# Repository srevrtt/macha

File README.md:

# Macha

Macha is currently a Work-In-Progress (WIP). I have not completely written this README
yet because this project is nowhere close to being finished and therefore I don't know
what features the eventual release will/will not have.

But basically, Macha will be a hypersonic, secure, and easy-to-use database/spreadhseet
application for my own personal and business use. The goal for now is not to make this
perfect for everyone; just trying to make it perfect for me first. :)

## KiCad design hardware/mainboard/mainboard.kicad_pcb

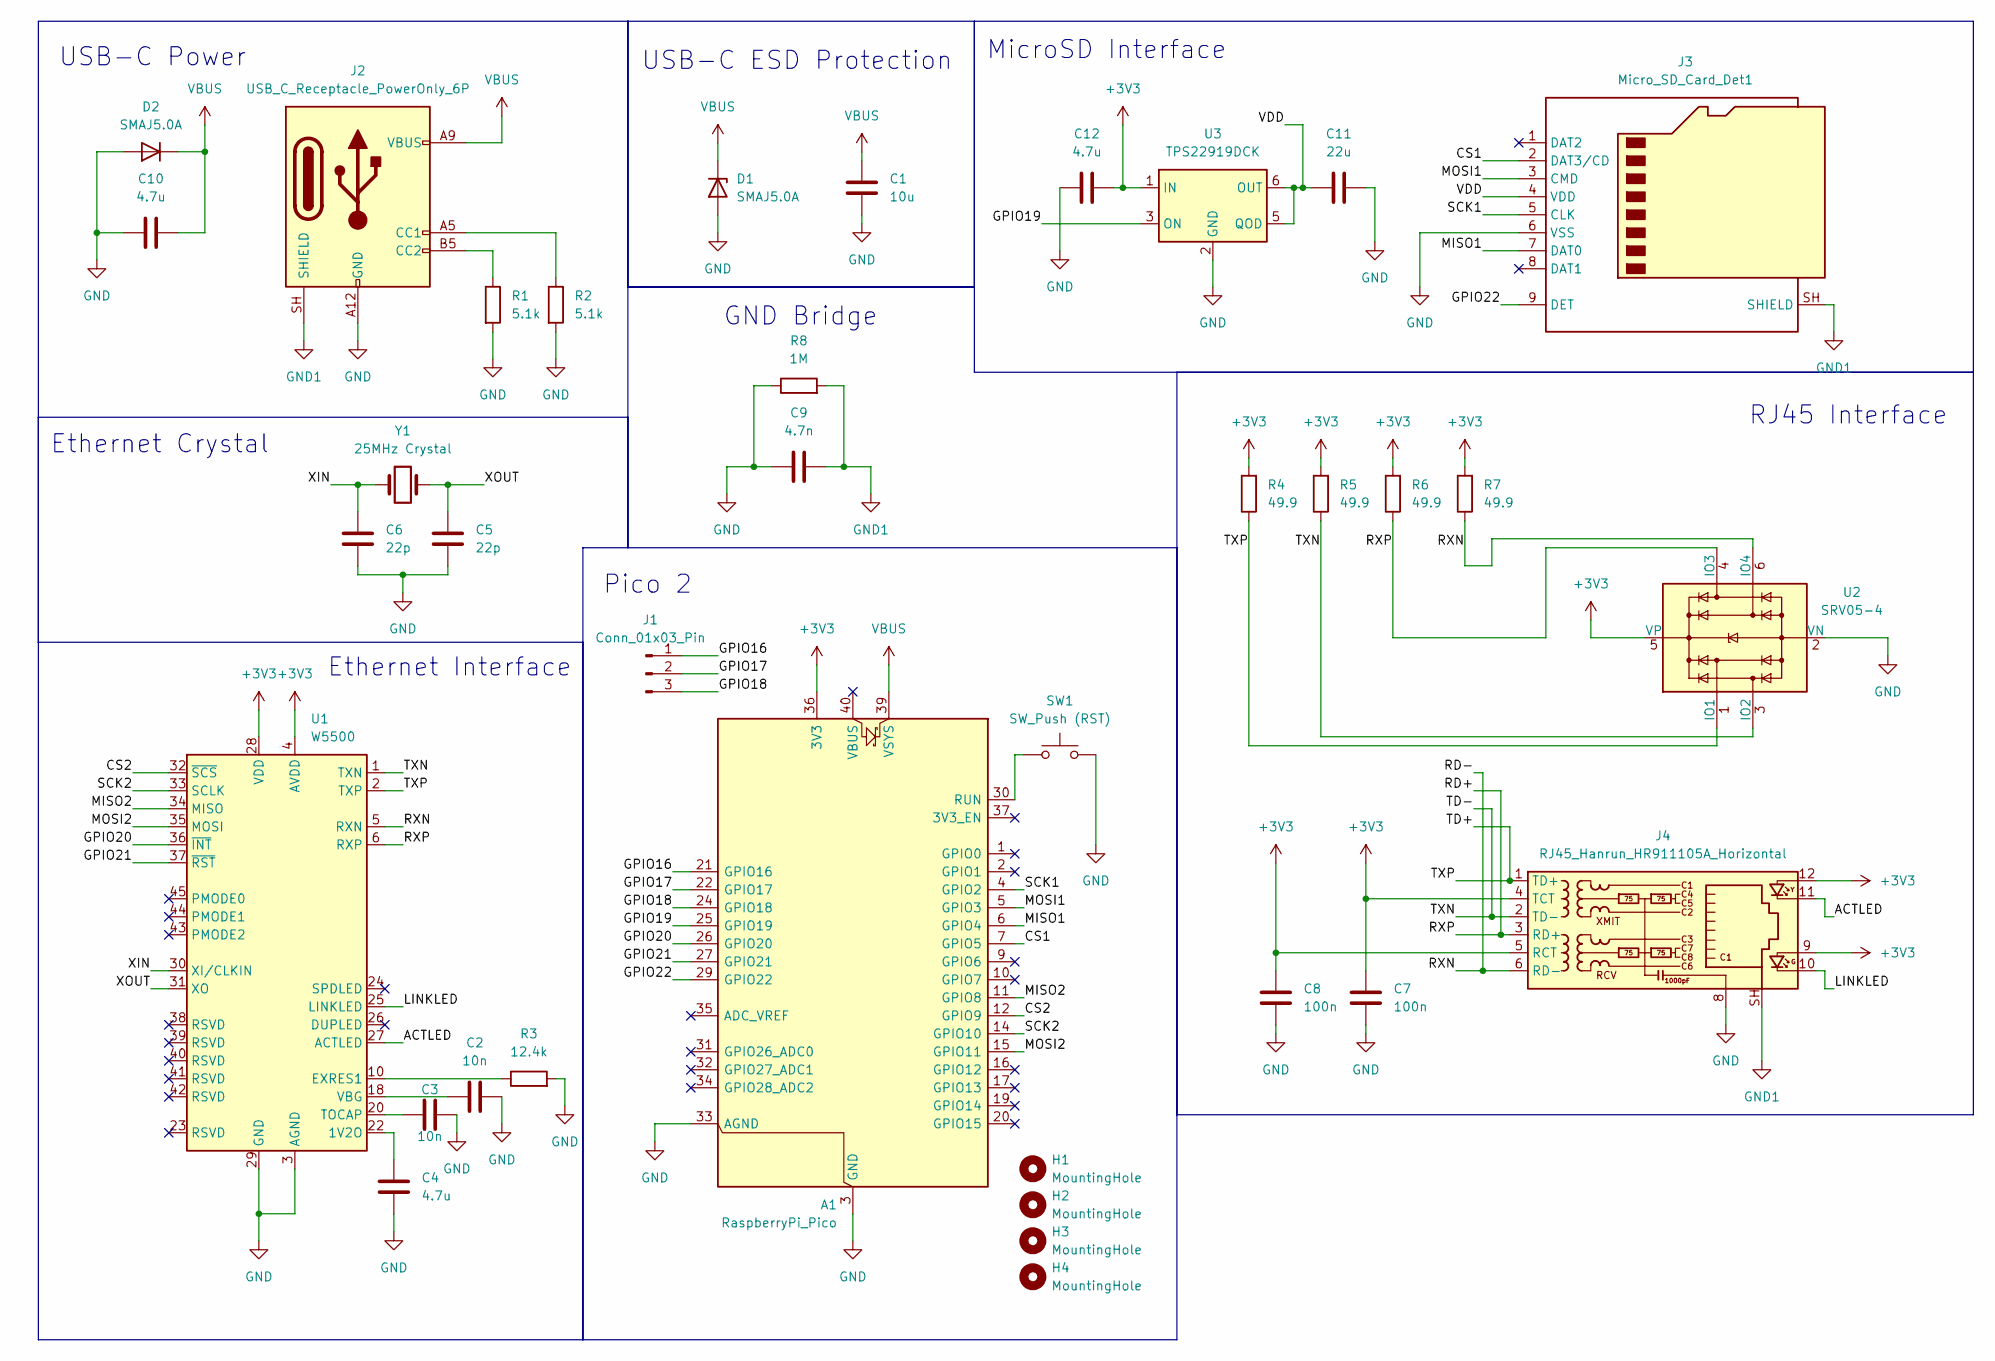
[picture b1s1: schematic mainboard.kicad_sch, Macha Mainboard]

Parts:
A1: RaspberryPi_Pico; RaspberryPi_Pico_Common_Unspecified
C1: 10u; C_0201_0603Metric
C2, C3: 10n; C_0201_0603Metric
C4, C10, C12: 4.7u; C_0805_2012Metric
C5, C6: 22p; C_0201_0603Metric
C7, C8: 100n; C_0603_1608Metric
C9: 4.7n; C_1812_4532Metric
C11: 22u; C_0201_0603Metric
D1, D2: SMAJ5.0A; D_SMA
H1, H2, H3, H4: MountingHole; MountingHole_2.2mm_M2
J1: Conn_01x03_Pin; PinHeader_1x03_P2.54mm_Vertical
J2: USB_C_Receptacle_PowerOnly_6P; USB_C_Receptacle_GCT_USB4125-xx-x-0190_6P_TopMnt_Horizontal
J3: Micro_SD_Card_Det1; microSD_HC_Hirose_DM3BT-DSF-PEJS
J4: RJ45_Hanrun_HR911105A_Horizontal
R1: 5.1k; R_0201_0603Metric_Pad0.64x0.40mm_HandSolder
R2: 5.1k; R_0603_1608Metric
R3: 12.4k; R_0603_1608Metric
R4, R5, R6, R7: 49.9; R_0603_1608Metric
R8: 1M; R_0603_1608Metric
SW1: SW_Push (RST); SW_PUSH_6mm
U1: W5500; LQFP-48_7x7mm_P0.5mm
U2: SRV05-4; SOT-23-6
U3: TPS22919DCK; SOT-363_SC-70-6
Y1: 25MHz Crystal; Crystal_SMD_3225-4Pin_3.2x2.5mm

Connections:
+3V3: A1.36 (3V3), C7.1, C8.1, C12.1, J4.4 (TCT), J4.5 (RCT), J4.9, J4.12, R4.2, R5.2, R6.2, R7.2, U1.4 (AVDD), U1.8 (AVDD), U1.11 (AVDD), U1.15 (AVDD), U1.17 (AVDD), U1.21 (AVDD), U1.28 (VDD), U2.5 (VP), U3.1 (IN)
/ACTLED: J4.11, U1.27 (ACTLED)
/CS1: A1.7 (GPIO5), J3.2 (DAT3/CD)
/CS2: A1.12 (GPIO9), U1.32 (~SCS)
/GPIO16: A1.21 (GPIO16), J1.1
/GPIO17: A1.22 (GPIO17), J1.2
/GPIO18: A1.24 (GPIO18), J1.3
/GPIO19: A1.25 (GPIO19), U3.3 (ON)
/GPIO20: A1.26 (GPIO20), U1.36 (~INT)
/GPIO21: A1.27 (GPIO21), U1.37 (~RST)
/GPIO22: A1.29 (GPIO22), J3.9 (DET)
/LINKLED: J4.10, U1.25 (LINKLED)
/MISO1: A1.6 (GPIO4), J3.7 (DAT0)
/MISO2: A1.11 (GPIO8), U1.34 (MISO)
/MOSI1: A1.5 (GPIO3), J3.3 (CMD)
/MOSI2: A1.15 (GPIO11), U1.35 (MOSI)
/RD+: J4.3 (RD+), R6.1, U1.6 (RXP), U2.4 (IO3)
/RD-: J4.6 (RD-), R7.1, U1.5 (RXN), U2.6 (IO4)
/SCK1: A1.4 (GPIO2), J3.5 (CLK)
/SCK2: A1.14 (GPIO10), U1.33 (SCLK)
/TD+: J4.1 (TD+), R4.1, U1.2 (TXP), U2.1 (IO1)
/TD-: J4.2 (TD-), R5.1, U1.1 (TXN), U2.3 (IO2)
/VDD: C11.1, J3.4 (VDD), U3.5 (QOD), U3.6 (OUT)
/XIN: C6.2, U1.30 (XI/CLKIN), Y1.1
/XOUT: C5.1, U1.31 (XO), Y1.2
GND: A1.3 (GND), A1.8 (GND), A1.13 (GND), A1.18 (GND), A1.23 (GND), A1.28 (GND), A1.33 (AGND), A1.38 (GND), C1.2, C2.2, C3.2, C4.1, C5.2, C6.1, C7.2, C8.2, C9.1, C10.2, C11.2, C12.2, D1.2 (A), D2.2 (A), J2.A12 (GND), J2.B12 (GND), J3.6 (VSS), J4.8, R1.2, R2.2, R3.2, R8.1, SW1.2, U1.3 (AGND), U1.9 (AGND), U1.14 (AGND), U1.16 (AGND), U1.19 (AGND), U1.29 (GND), U1.48 (AGND), U2.2 (VN), U3.2 (GND)
GND1: C9.2, J2.SH (SHIELD), J3.SH (SHIELD), J4.SH, R8.2
unnamed: A1.30 (RUN), SW1.1
unnamed: J2.A5 (CC1), R2.1
unnamed: J2.B5 (CC2), R1.1
unnamed: C4.2, U1.22 (1V2O)
unnamed: R3.1, U1.10 (EXRES1)
unnamed: C3.1, U1.20 (TOCAP)
unnamed: C2.1, U1.18 (VBG)
VBUS: A1.39 (VSYS), C1.1, C10.1, D1.1 (K), D2.1 (K), J2.A9 (VBUS), J2.B9 (VBUS)

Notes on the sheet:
RJ45 Interface
MicroSD Interface
Ethernet Interface
Pico 2
USB-C Power
USB-C ESD Protection
GND Bridge
Ethernet Crystal

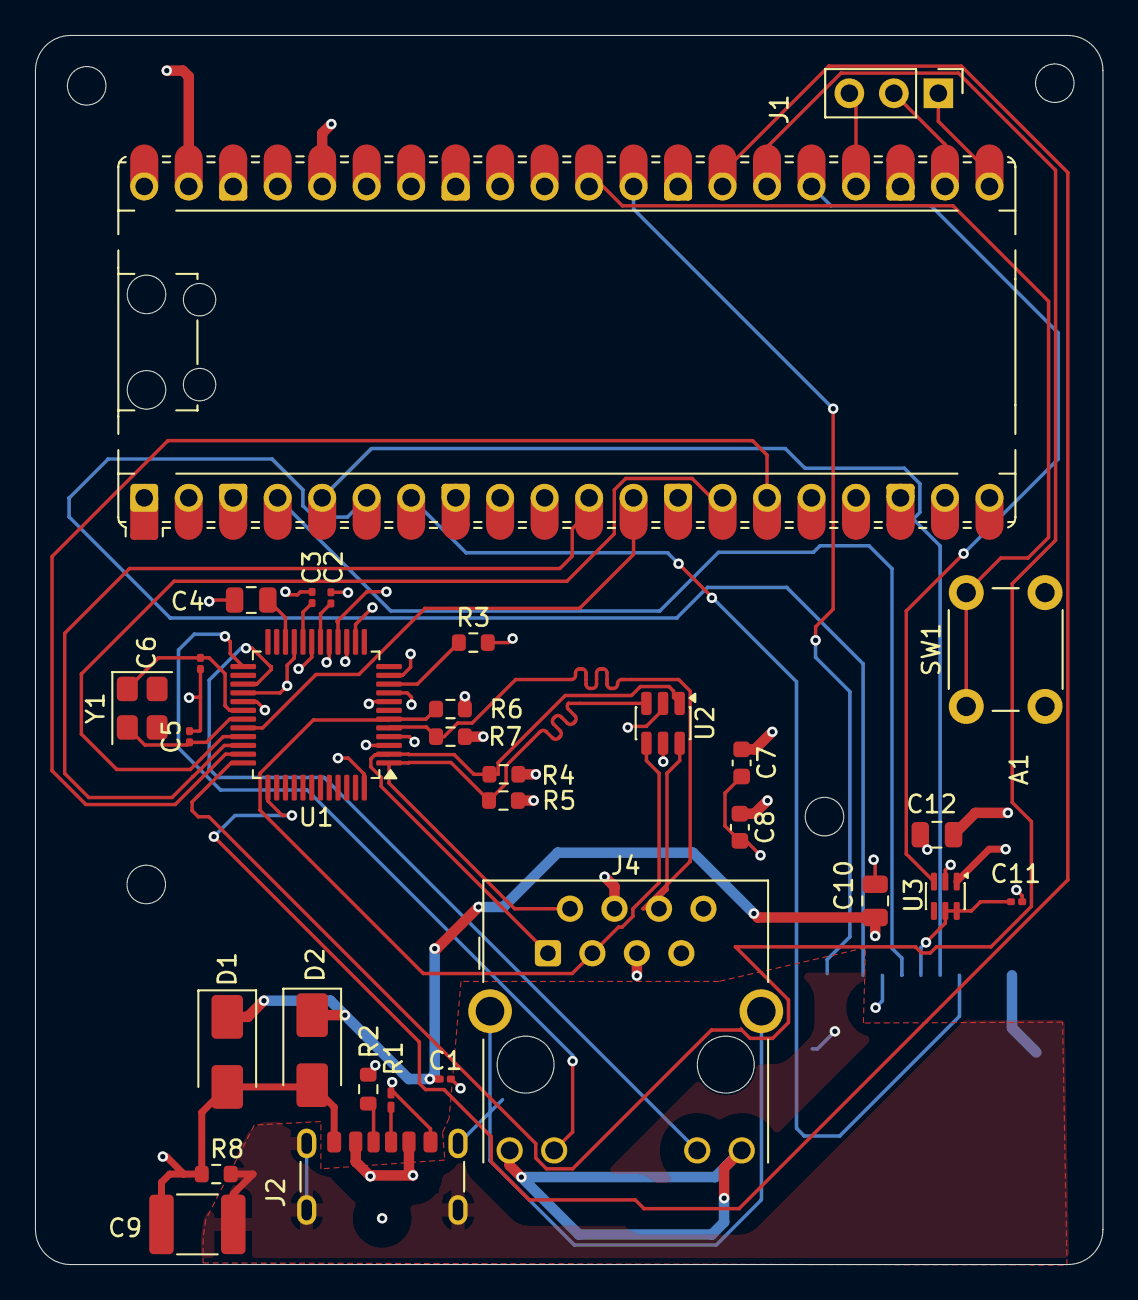
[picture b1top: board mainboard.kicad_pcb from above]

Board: 4 copper layers, 60.9 x 70.2 mm, 36 parts (1 on the bottom side), 35 nets.
